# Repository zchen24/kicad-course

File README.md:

# kicad-course
This repo stores the three KiCAD projects in Tech Explorations KiCad like a Pro course (Highly Recommend).

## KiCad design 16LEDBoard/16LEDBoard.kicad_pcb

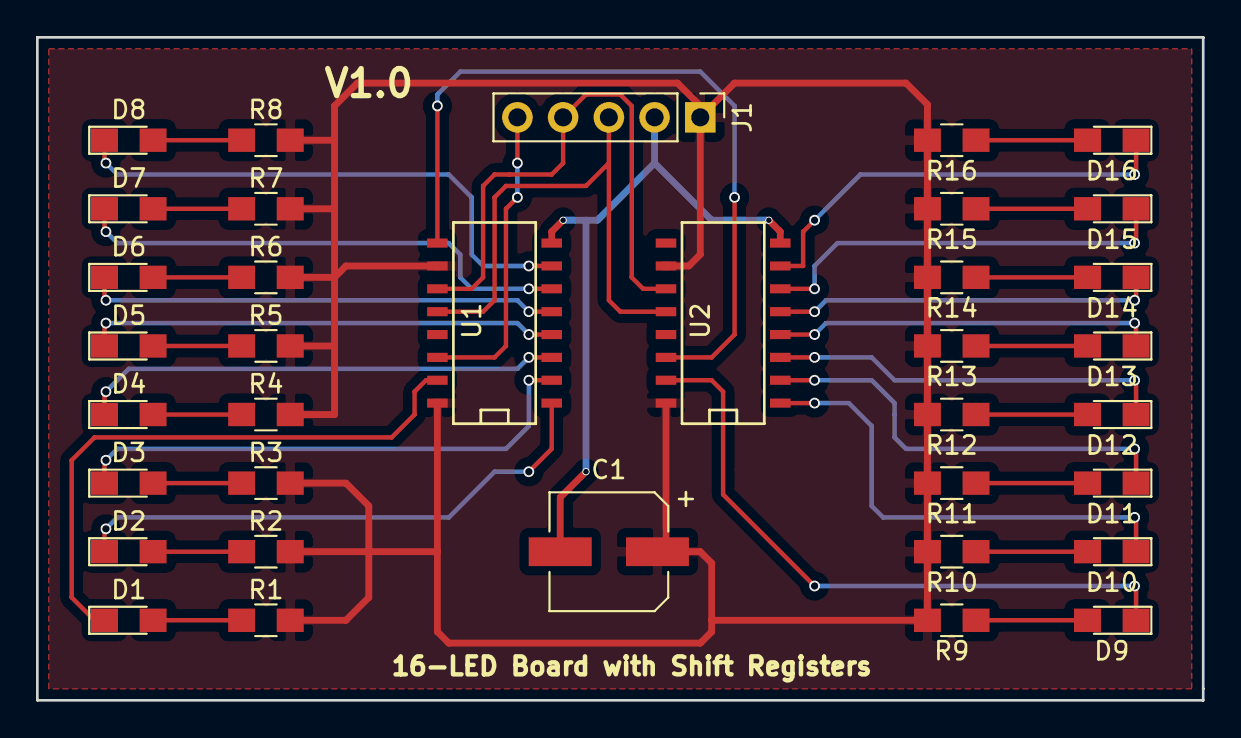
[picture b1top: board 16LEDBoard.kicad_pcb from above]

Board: 2 copper layers, 64.8 x 36.8 mm, 36 parts (0 on the bottom side), 38 nets.

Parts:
C1: 200uF; CP_Elec_6.3x5.3
D1, D2, D3, D4, D5, D6, D7, D8, D9, D10, D11, D12, D13, D14, D15, D16: LED; LED_0805_HandSoldering
J1: Conn_01x05; Pin_Header_Straight_1x05_Pitch2.54mm
R1, R2, R3, R4, R5, R6, R7, R8, R9, R10, R11, R12, R13, R14, R15, R16: 220 Ohm; R_0805_HandSoldering
U1, U2: 74HC595; SO-16-N

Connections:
/CLOCK: J1.4, U1.11, U2.11
/DATA: J1.5, U1.14
/DATA_S: U1.9, U2.14
/LATCH: J1.3, U1.12, U2.12
GND: C1.2, J1.2, U1.8, U2.8
unnamed: D1.1, U1.15
unnamed: D1.2, R1.1
unnamed: D2.1, U1.1
unnamed: D2.2, R2.1
unnamed: D3.1, U1.2
unnamed: D3.2, R3.1
unnamed: D4.1, U1.3
unnamed: D4.2, R4.1
unnamed: D5.1, U1.4
unnamed: D5.2, R5.1
unnamed: D6.1, U1.5
unnamed: D6.2, R6.1
unnamed: D7.1, U1.6
unnamed: D7.2, R7.1
unnamed: D8.1, U1.7
unnamed: D8.2, R8.1
unnamed: D9.1, U2.15
unnamed: D9.2, R9.1
unnamed: D10.1, U2.1
unnamed: D10.2, R10.1
unnamed: D11.1, U2.2
unnamed: D11.2, R11.1
unnamed: D12.1, U2.3
unnamed: D12.2, R12.1
unnamed: D13.1, U2.4
unnamed: D13.2, R13.1
unnamed: D14.1, U2.5
unnamed: D14.2, R14.1
unnamed: D15.1, U2.6
unnamed: D15.2, R15.1
unnamed: D16.1, U2.7
unnamed: D16.2, R16.1
VCC: C1.1, J1.1, R1.2, R2.2, R3.2, R4.2, R5.2, R6.2, R7.2, R8.2, R9.2, R10.2, R11.2, R12.2, R13.2, R14.2, R15.2, R16.2, U1.10, U1.16, U2.10, U2.16

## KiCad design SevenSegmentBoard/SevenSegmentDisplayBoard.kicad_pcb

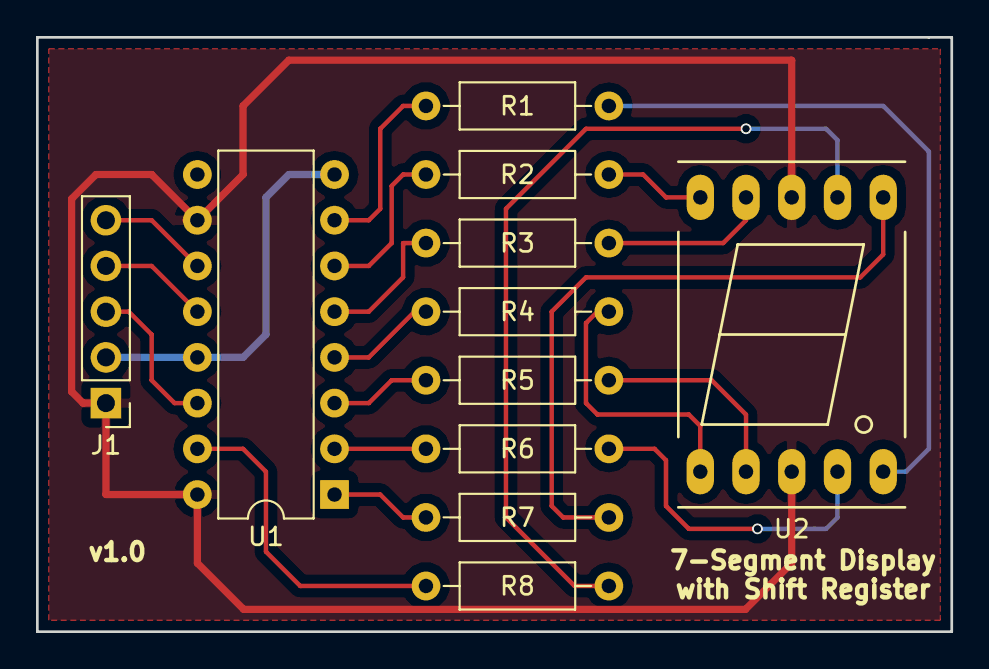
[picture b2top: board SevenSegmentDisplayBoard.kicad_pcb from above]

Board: 2 copper layers, 50.8 x 33.0 mm, 11 parts (0 on the bottom side), 21 nets.

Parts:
J1: Conn_01x05; Pin_Header_Straight_1x05_Pitch2.54mm
R1, R2, R3, R4, R5, R6, R7, R8: 220 Ohm; R_Axial_DIN0207_L6.3mm_D2.5mm_P10.16mm_Horizontal
U1: 74HC595; DIP-16_W7.62mm
U2: 7SEGMENT_CA; 7SegmentLED_LTS6760_LTS6780

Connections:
/CLOCK: J1.4, U1.12
/DATA: J1.5, U1.11
/LATCH: J1.3, U1.14
/sg0: R8.1, U1.15
/sg1: R7.1, U1.1
/sg2: R6.1, U1.2
/sg3: R5.1, U1.3
/sg4: R4.1, U1.4
/sg5: R3.1, U1.5
/sg6: R2.1, U1.6
/sg7: R1.1, U1.7
GND: J1.2, U1.8, U1.13
unnamed: R1.2, U2.5
unnamed: R2.2, U2.10
unnamed: R3.2, U2.9
unnamed: R4.2, U2.1
unnamed: R5.2, U2.2
unnamed: R6.2, U2.4
unnamed: R7.2, U2.6
unnamed: R8.2, U2.7
VCC: J1.1, U1.10, U1.16, U2.3, U2.8

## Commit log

2018-06-16 Added inital SevenSegmentBoard project
2018-06-16 Added finished alpha version
2018-06-16 Added 16 LED board
2018-06-17 Added finished 16-LED board design
2018-06-18 Added README file
